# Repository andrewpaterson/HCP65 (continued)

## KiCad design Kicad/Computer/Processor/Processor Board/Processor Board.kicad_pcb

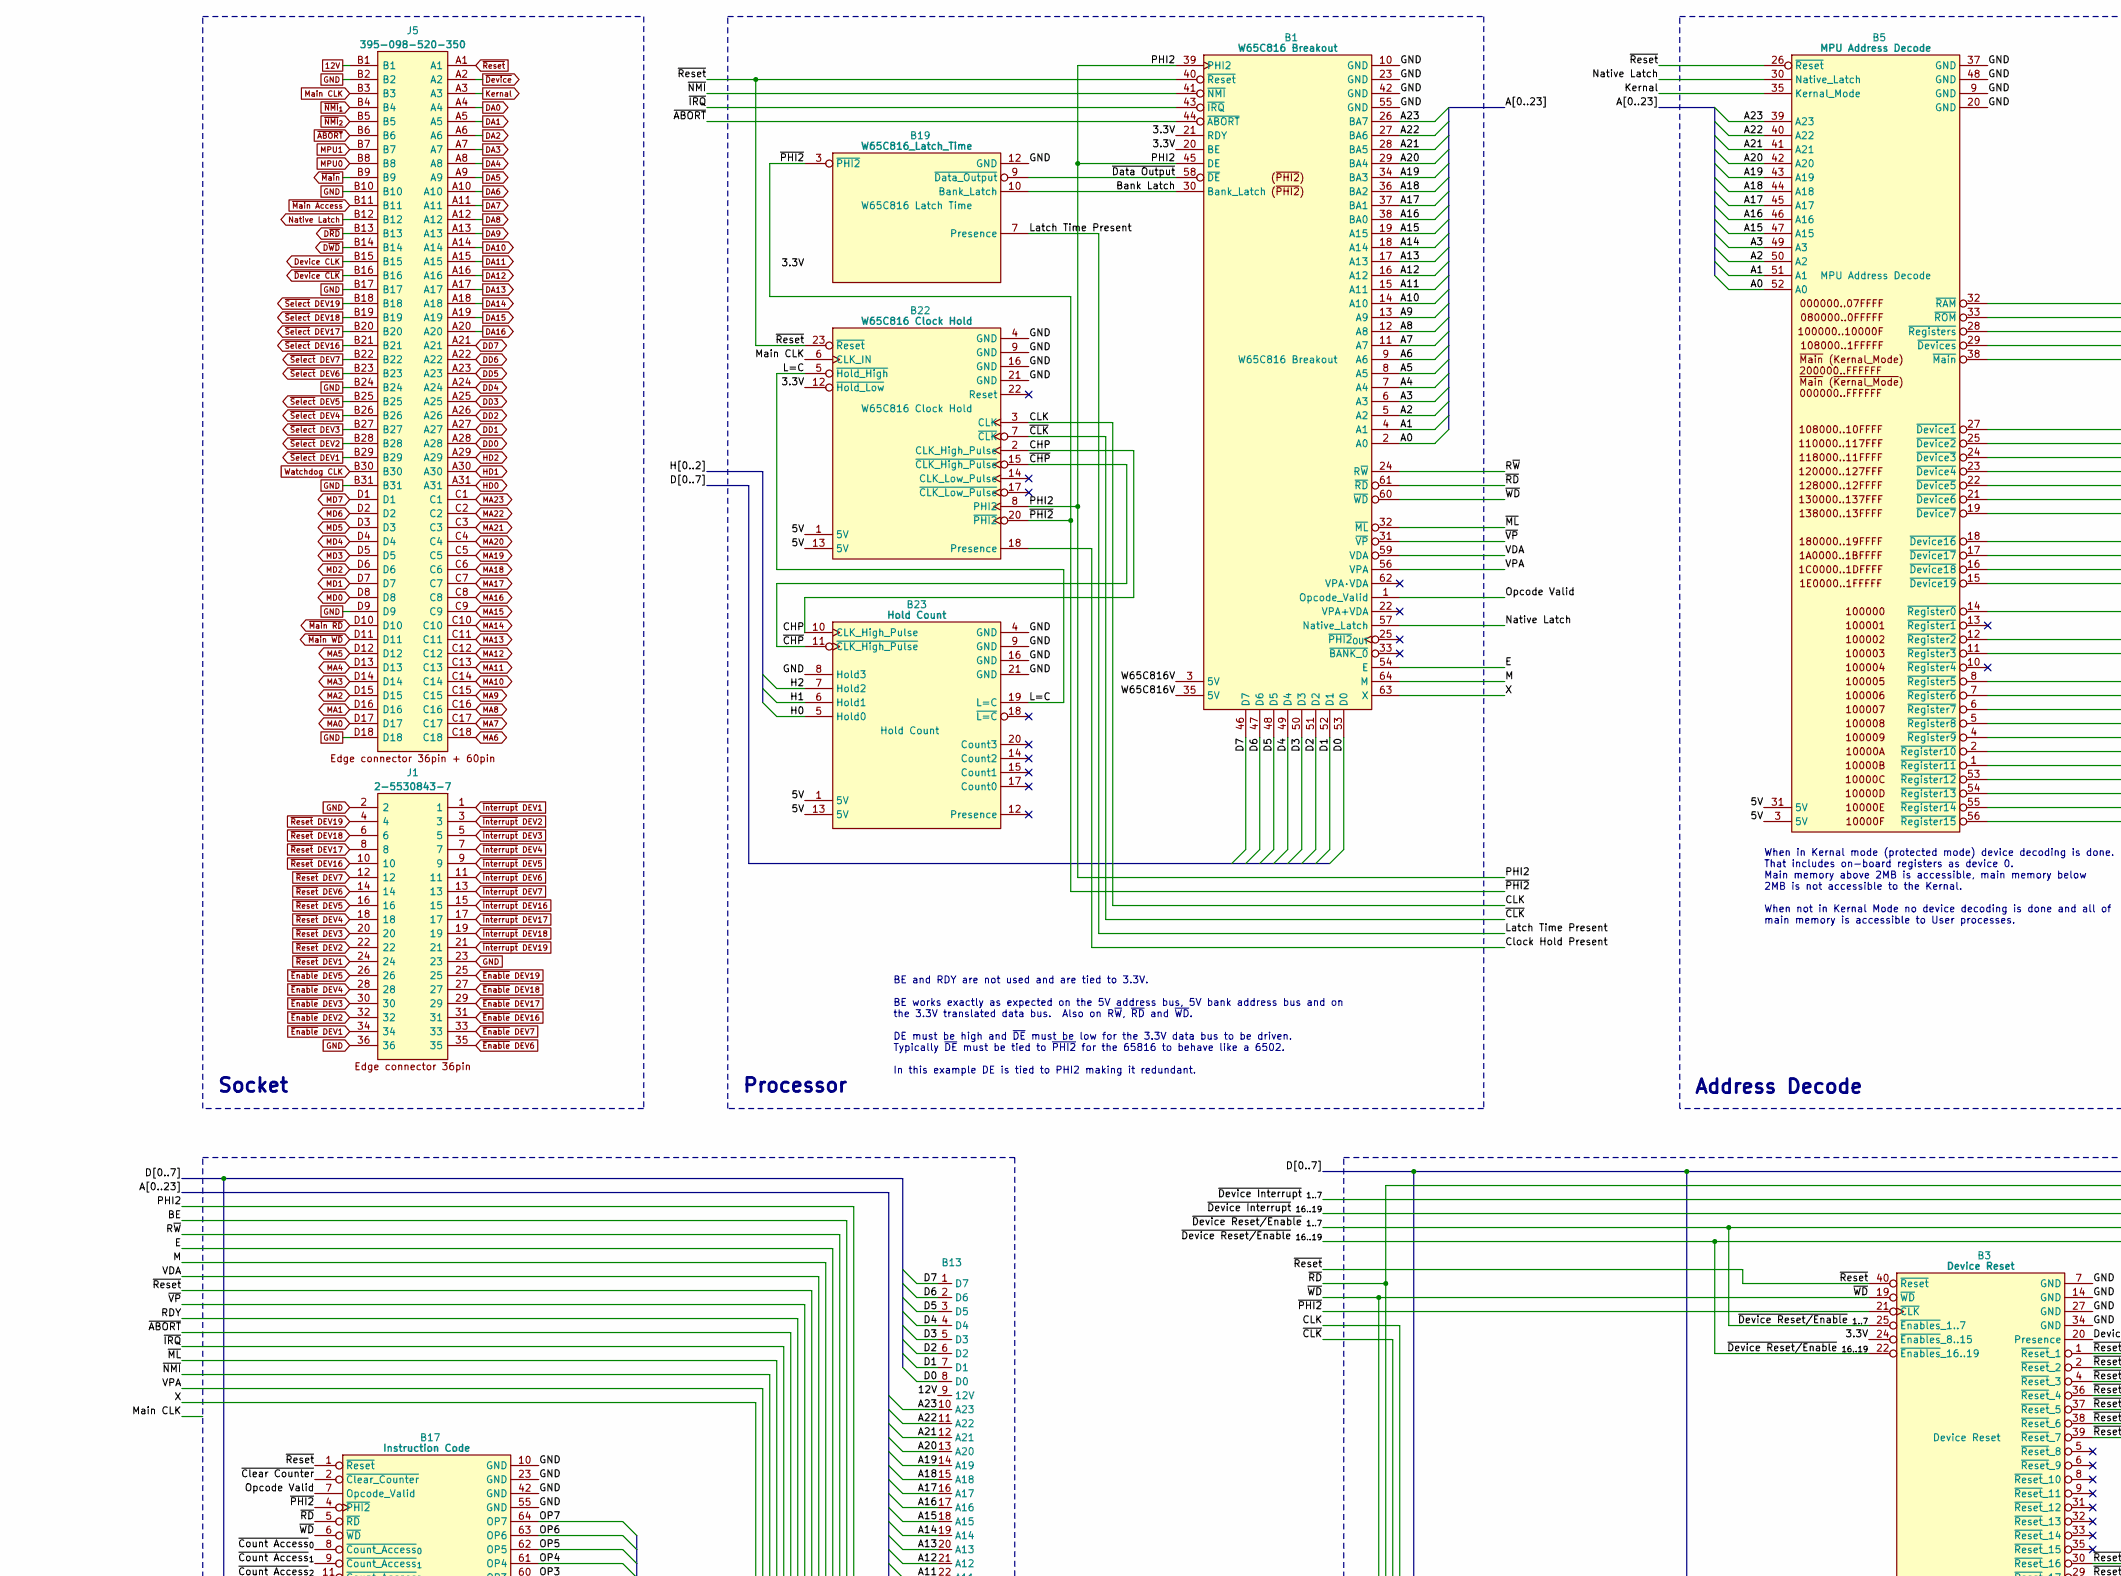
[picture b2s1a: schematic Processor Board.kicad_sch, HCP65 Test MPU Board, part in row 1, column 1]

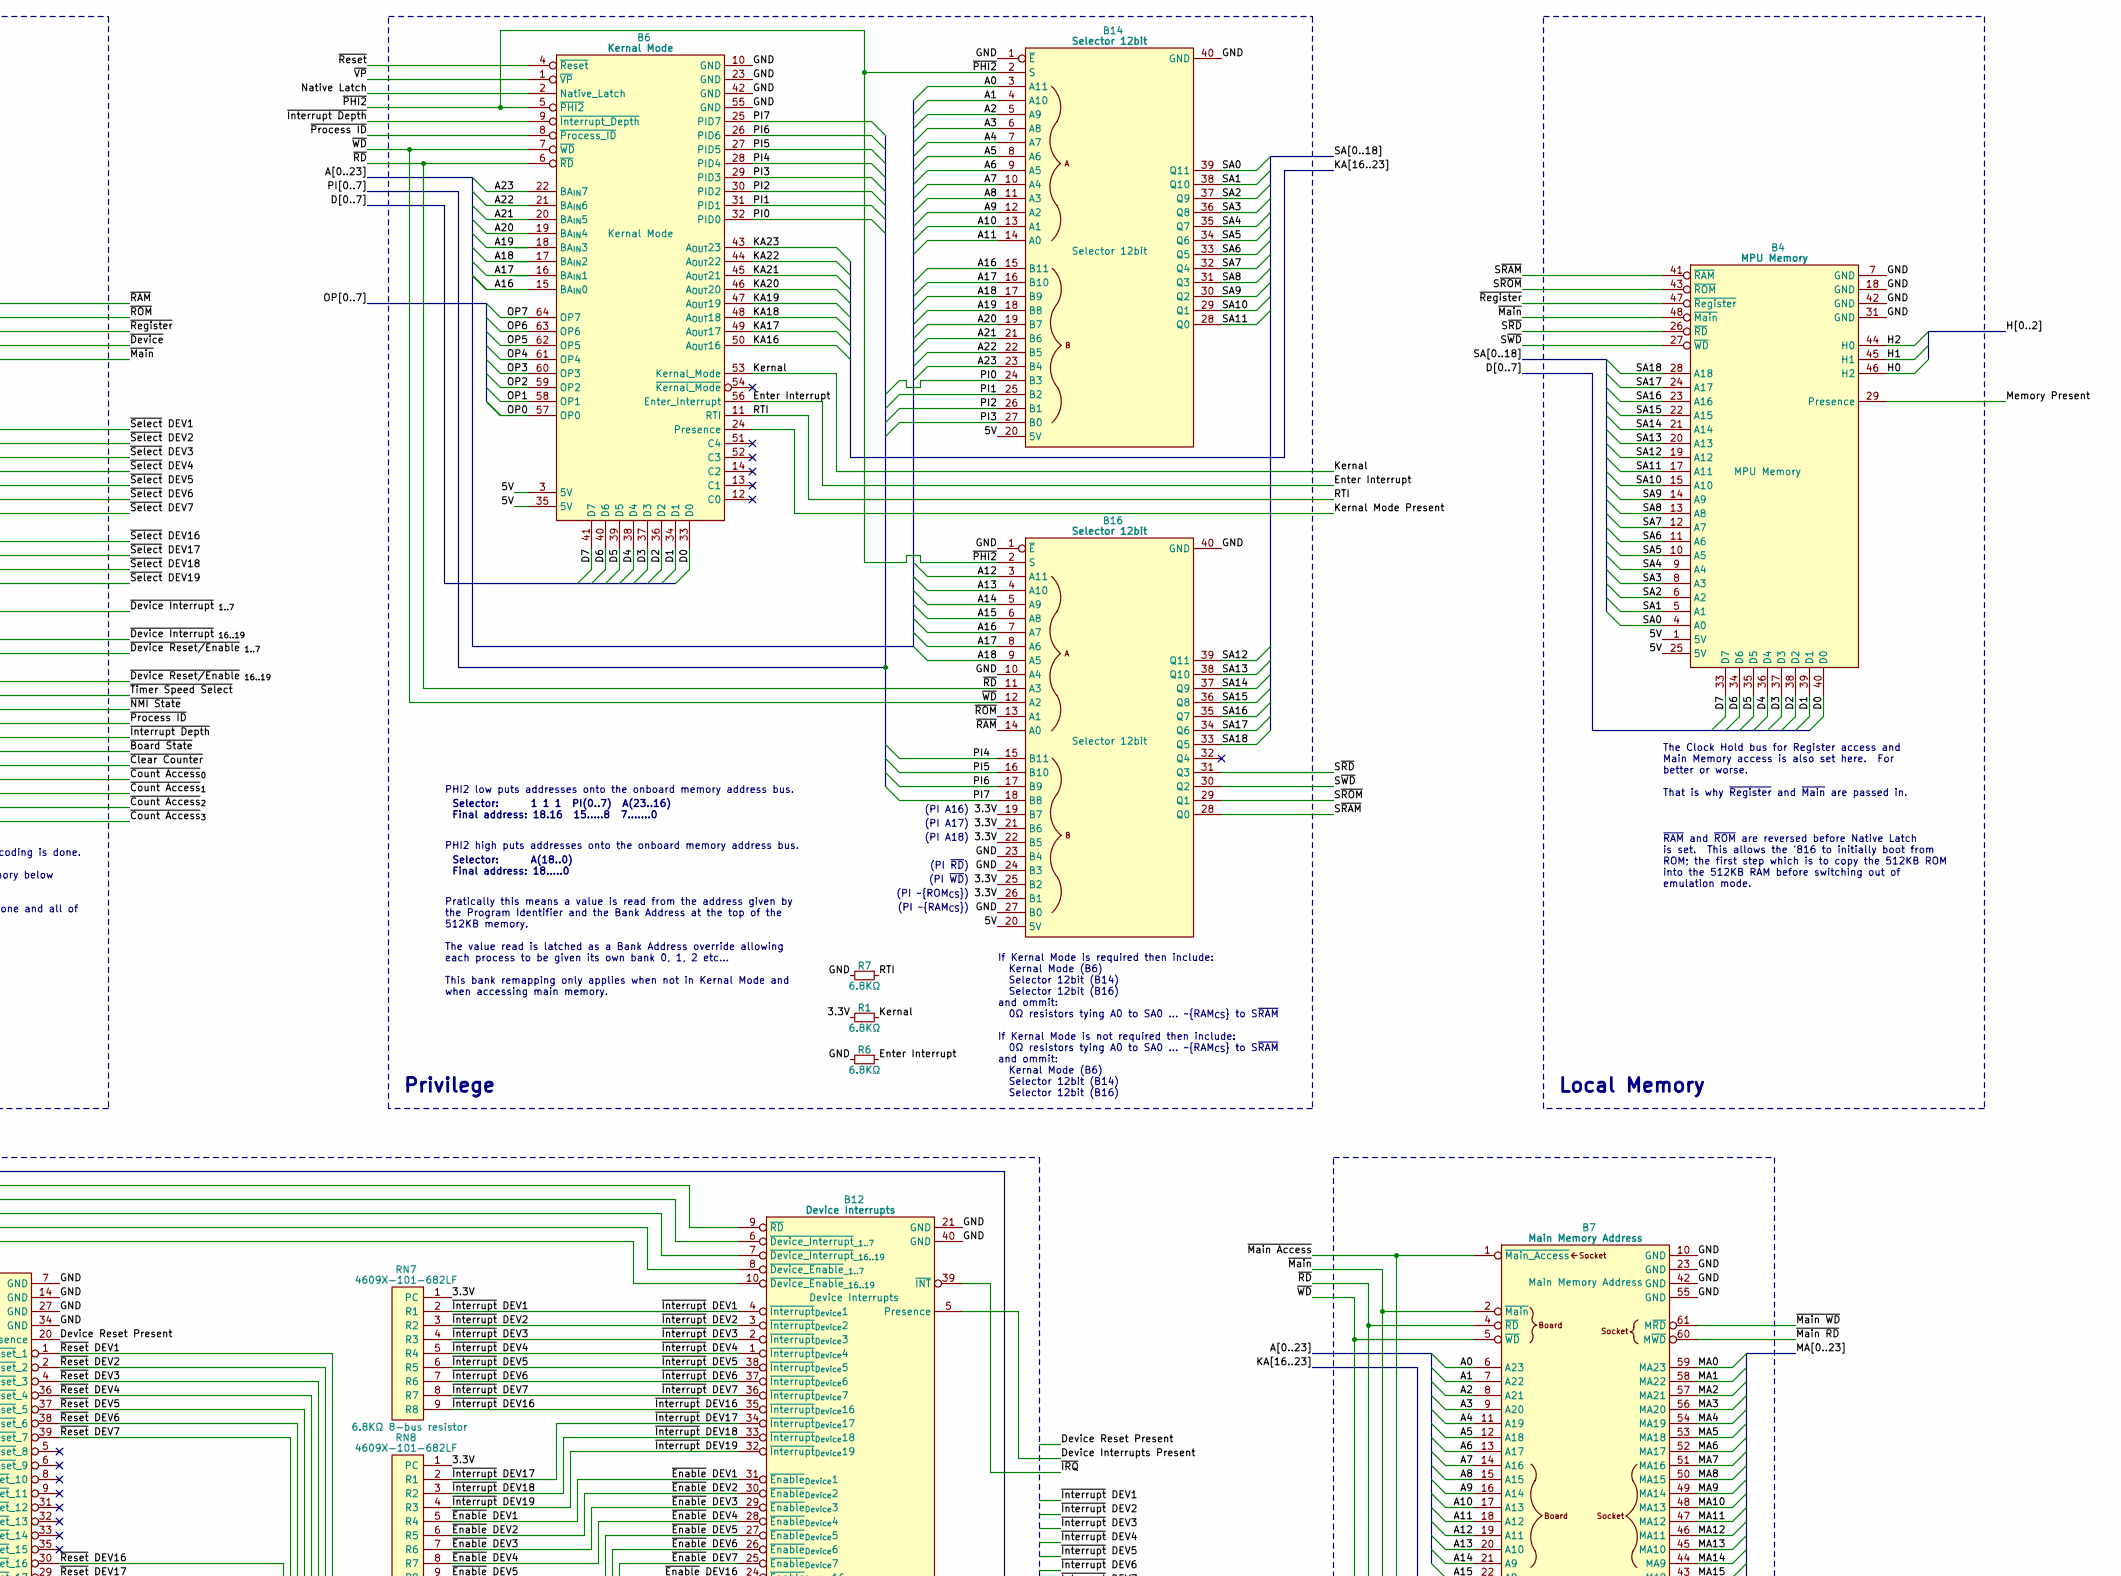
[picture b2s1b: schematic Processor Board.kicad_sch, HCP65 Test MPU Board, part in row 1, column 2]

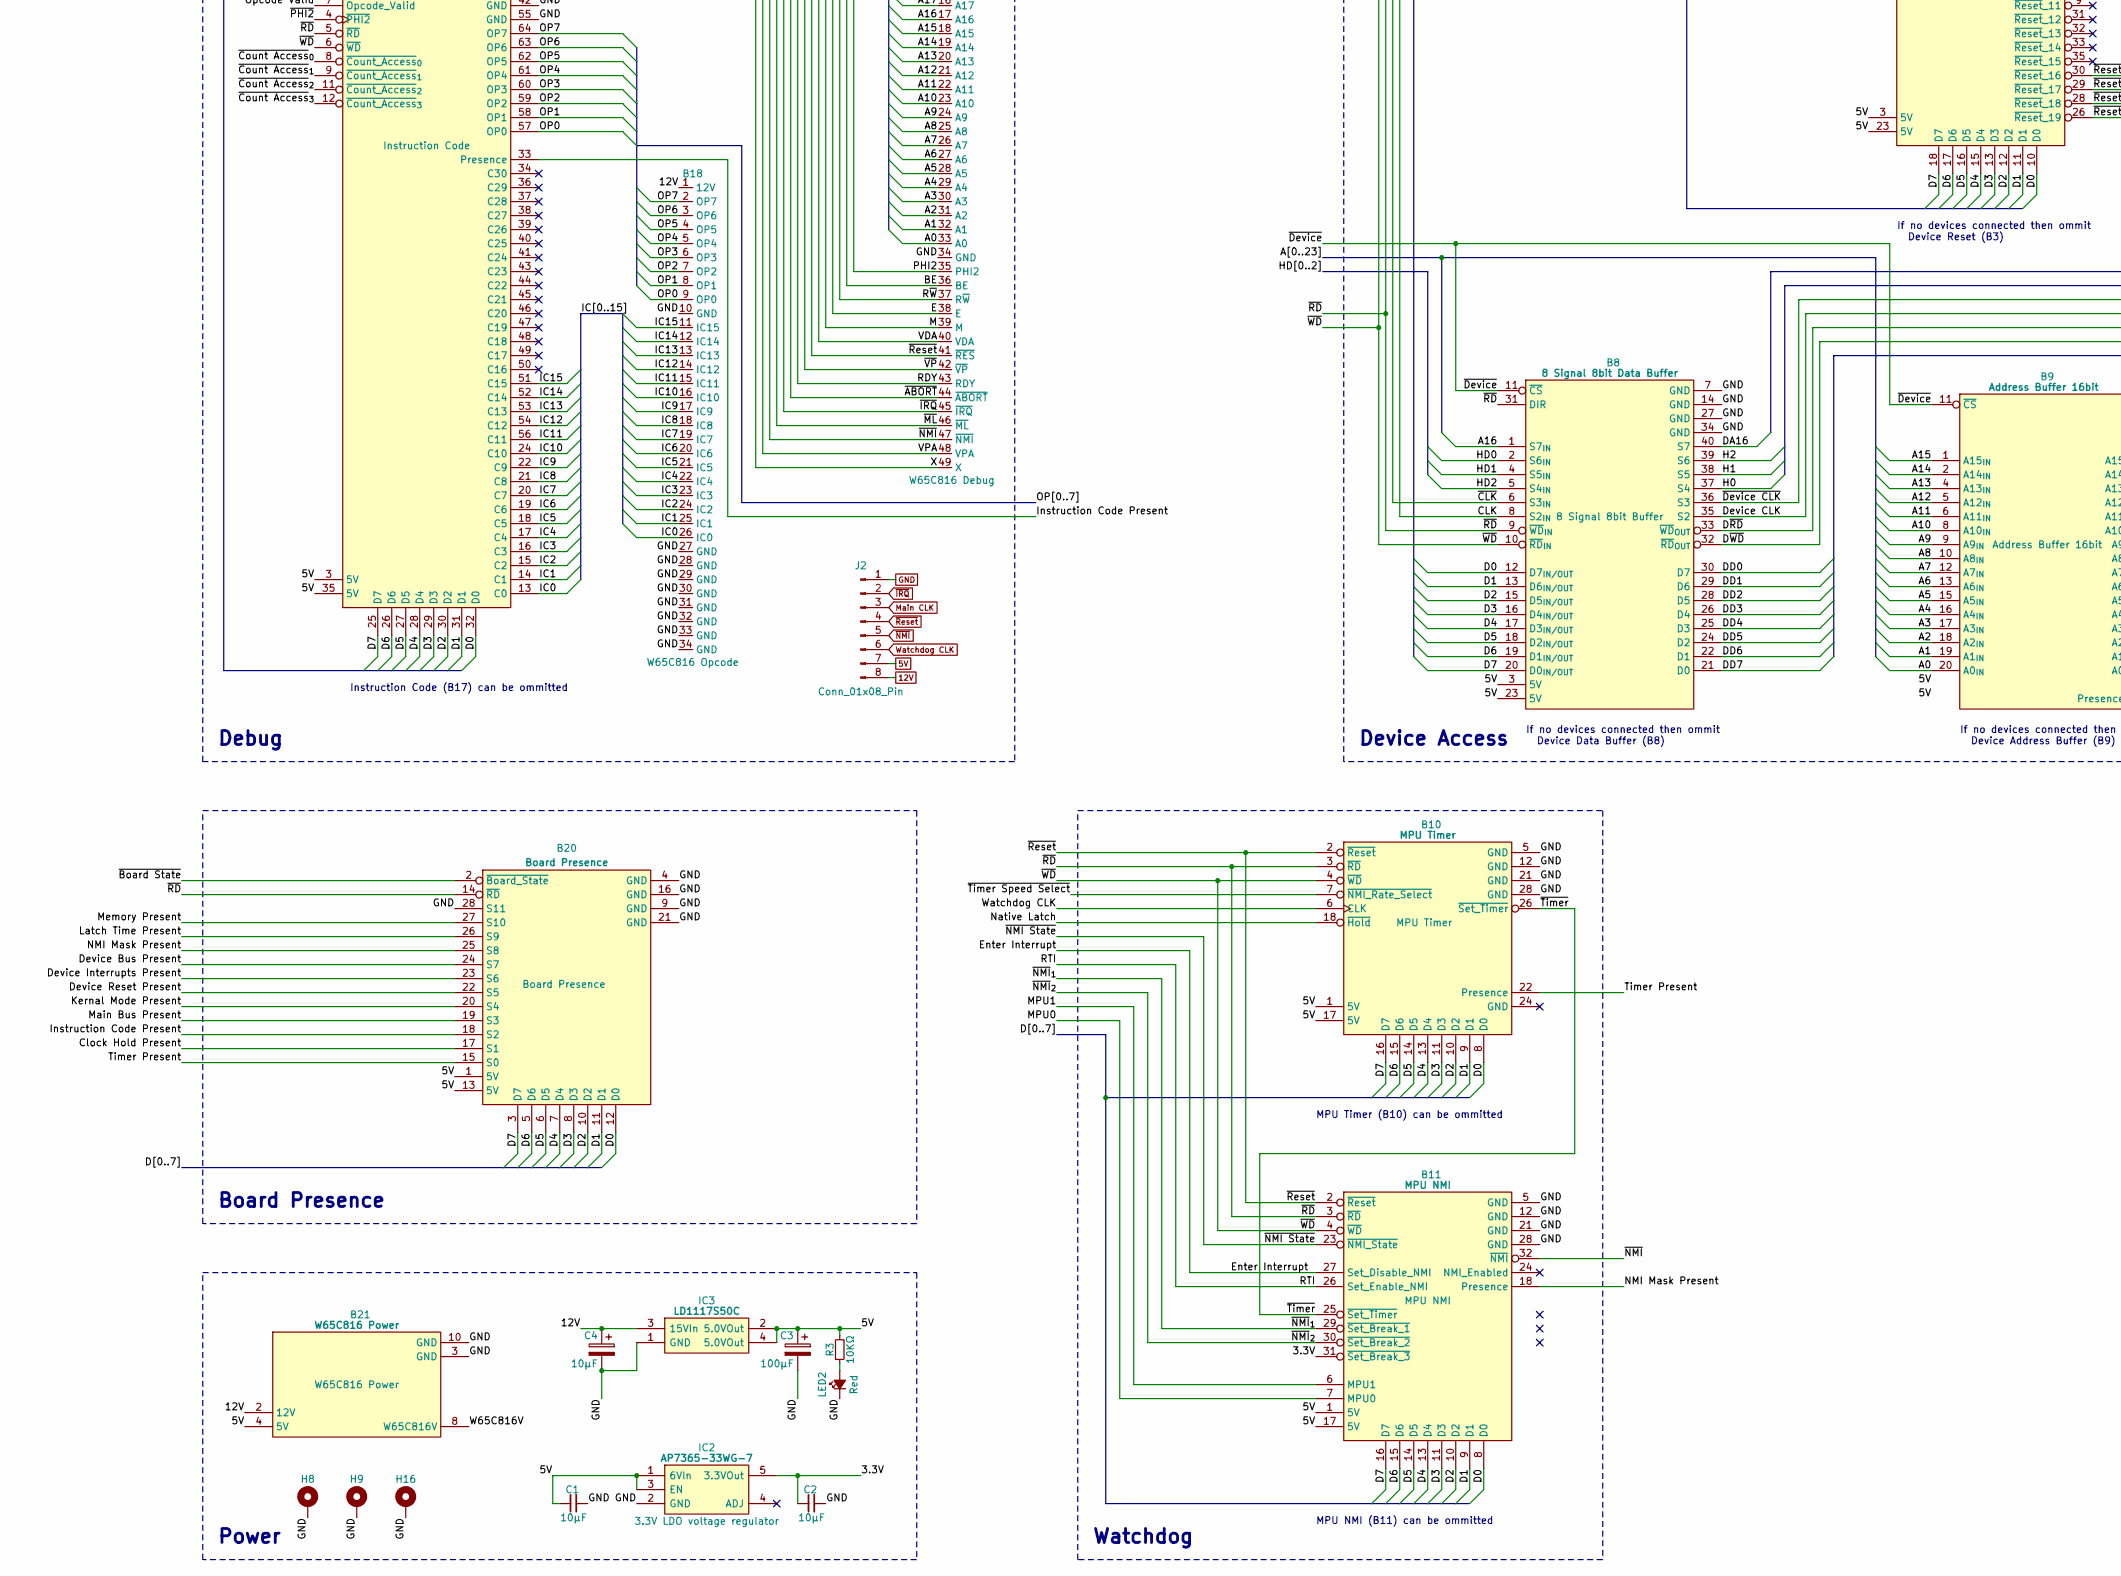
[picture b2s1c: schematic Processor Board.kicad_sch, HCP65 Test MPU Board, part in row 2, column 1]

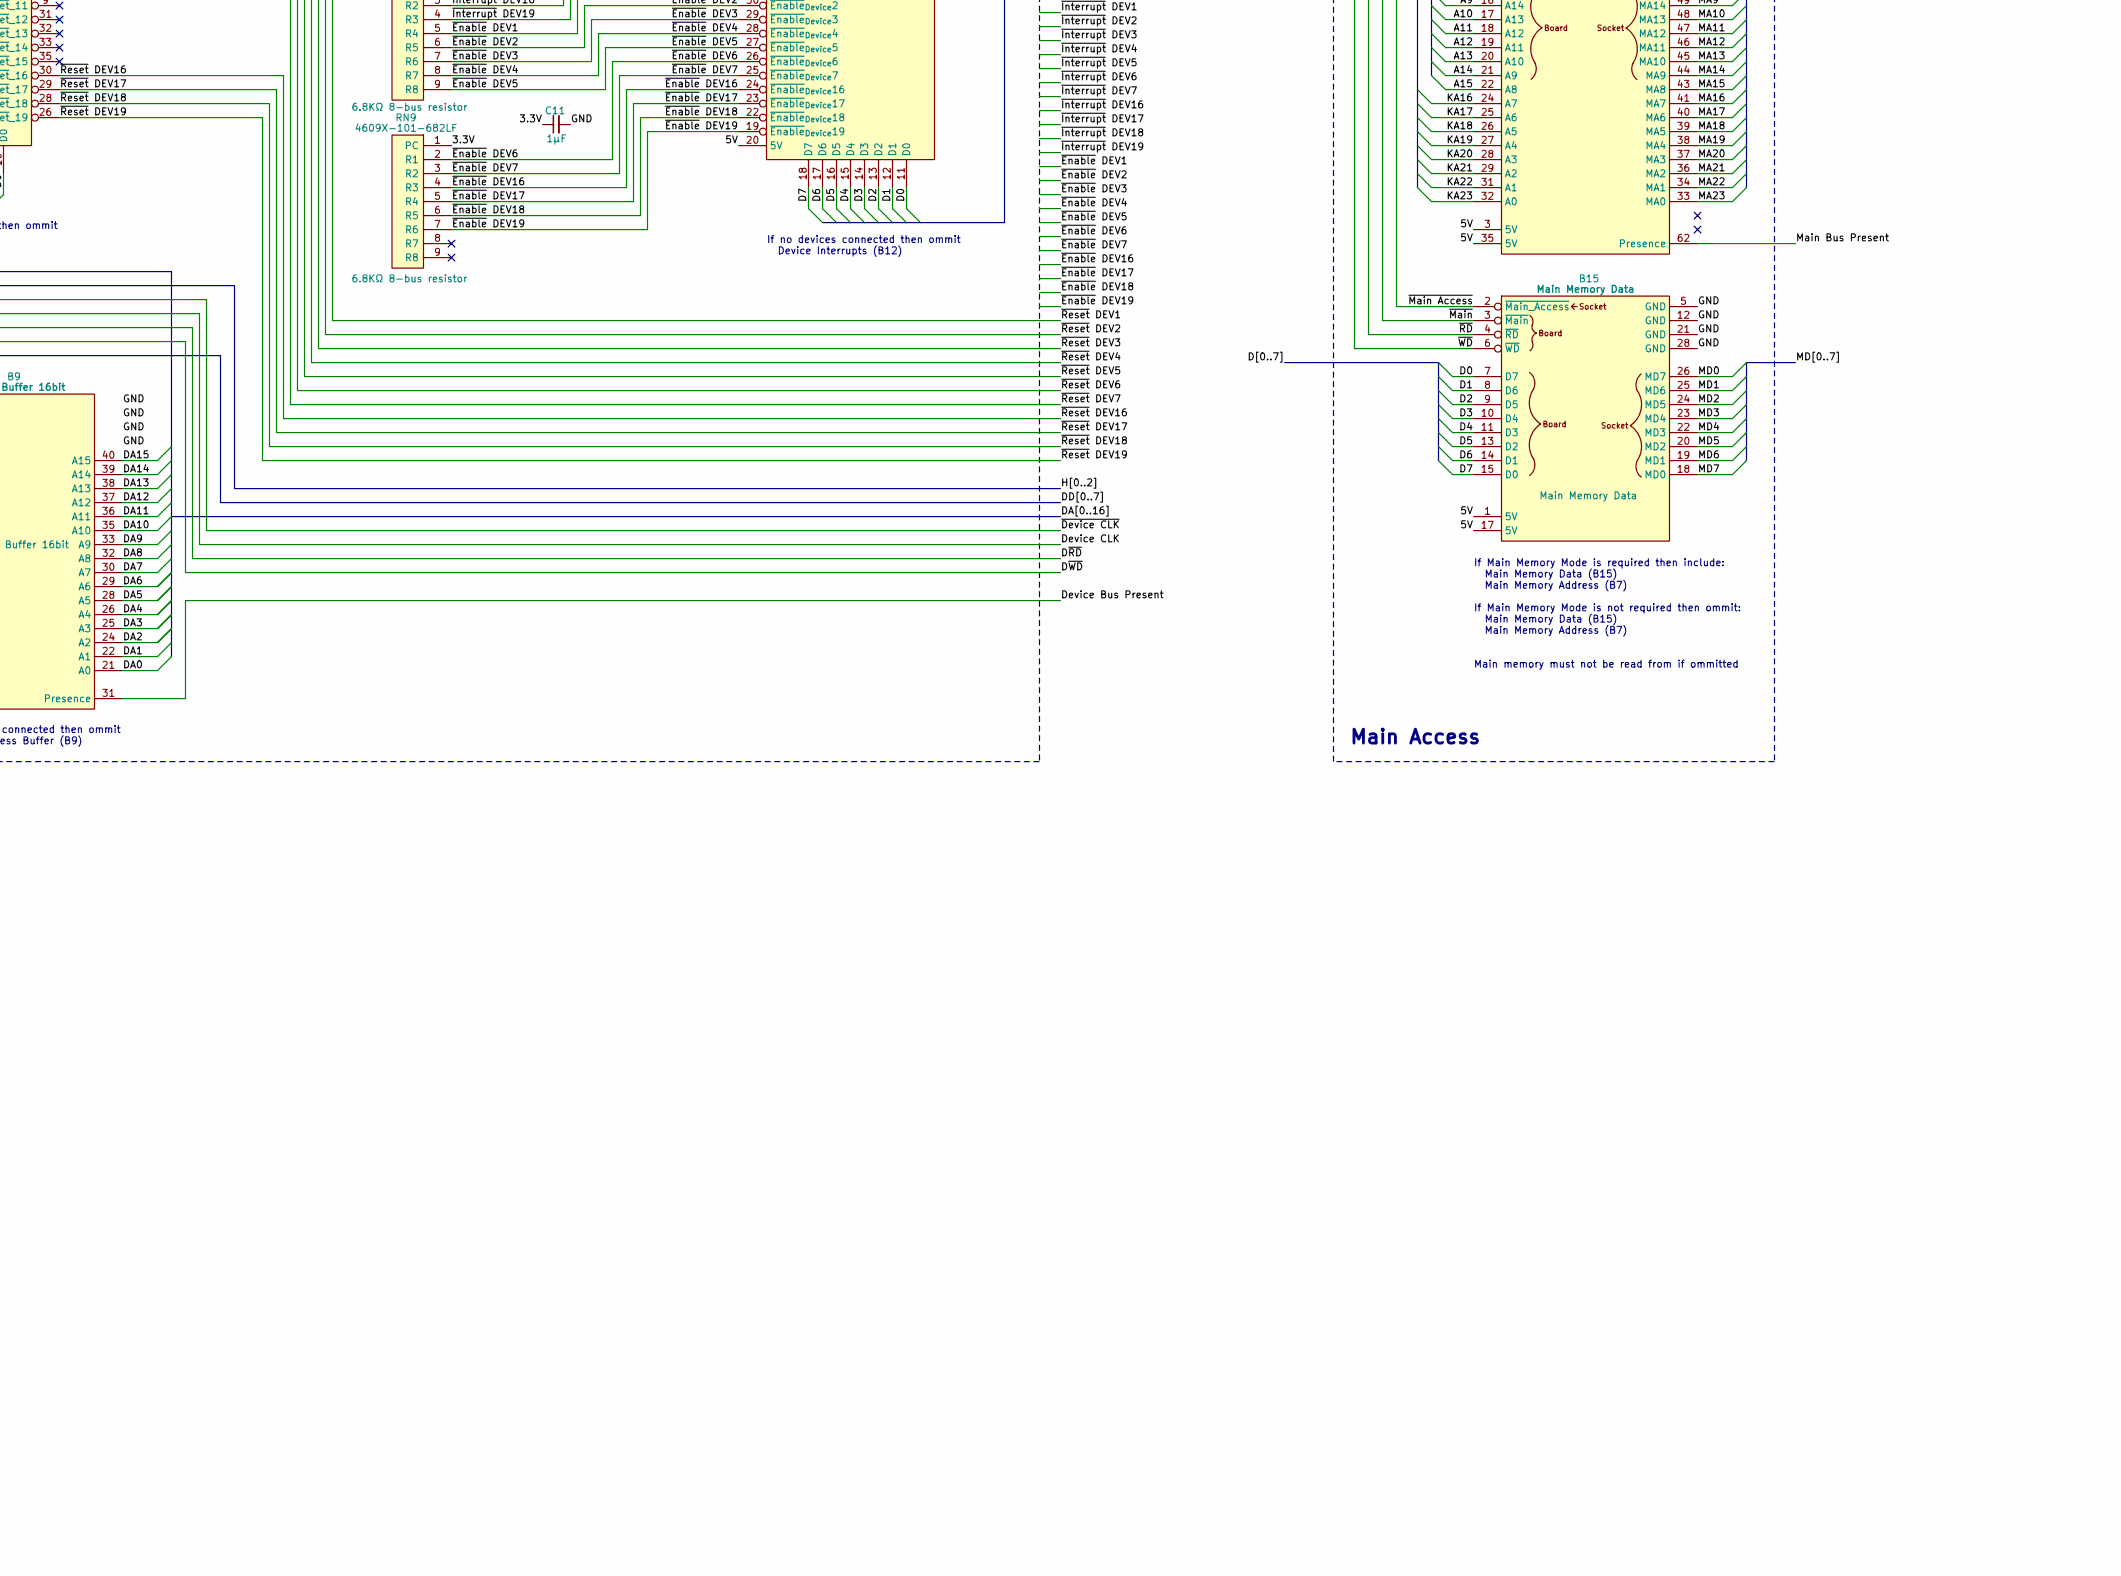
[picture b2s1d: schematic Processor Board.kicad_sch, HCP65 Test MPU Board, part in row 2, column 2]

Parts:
B1: W65C816 Breakout; HCP65_W65C816_Breakout
B3: Device Reset; HCP65_Device_Reset
B4: MPU Memory; HCP65_MPU_Memory
B5: MPU Address Decode; HCP65_MPU_Address_Decode
B6: Kernal Mode; HCP65_Kernal_Mode
B7: Main Memory Address; HCP65_Main_Memory_Address
B8: 8 Signal 8bit Data Buffer; HCP65_Data_and_Signal_Buffer
B9: Address Buffer 16bit; HCP65_Address_Buffer_16bit
B10: MPU Timer; HCP65_MPU_Timer
B11: MPU NMI; HCP65_MPU_NMI
B12: Device Interrupts; HCP65_Device_Interrupts
B13: W65C816 Debug; HCP65_W65C816_Debug_Display
B14, B16: Selector 12bit; HCP65_Selector_12bit
B15: Main Memory Data; HCP65_Main_Memory_Data
B17: Instruction Code; HCP65_Instruction_Code
B18: W65C816 Opcode; HCP65_W65C816_Debug_Instruction
B19: W65C816_Latch_Time; HCP65_W65C816_Latch_Time
B20: Board Presence; HCP65_Board_Presence
B21: W65C816 Power; HCP65_W65C816_Power
B22: W65C816 Clock Hold; HCP65_W65C816_Clock_Hold
B23: Hold Count; HCP65_Hold_Count
C1, C2: 10µF; C_0805
C3: 100μF; CP_Radial_D4.0mm_P2.00mm
C4: 10μF; CP_Radial_D4.0mm_P2.00mm
C11: 1μF; C_0805
H8, H9, H16: MountingHole_Pad; HCP65_MountingHole_M3_
IC2: AP7365-33WG-7; SOT95P285X130-5N; Manufacturer_Part_Number AP7365-33WG-7; Mouser Part Number 621-AP7365-33WG-7
IC3: LD1117S50C; LD1117S33C; Manufacturer_Part_Number LD1117S50C
J1: 2-5530843-7; 36pin Edge Connector; Manufacturer_Part_Number 2-5530843-7; Mouser Part Number 571-2-5530843-7
J2: Conn_01x08_Pin; PinHeader_1x08_P2.54mm_Vertical
J5: 395-098-520-350; 98pin Edge Connector; Manufacturer_Part_Number 395-098-520-350; Mouser Part Number 587-395-098-520-350
LED2: Red; LED_D5.0mm
R1, R6, R7: 6.8KΩ; R_0805
R3: 10KΩ; R_0805
RN7, RN8, RN9: 4609X-101-682LF; 4609X; Manufacturer_Part_Number 4609X-101-682LF; Mouser Part Number 652-4609X-1LF-6.8K

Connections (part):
5V: B3.3 (5V), B3.23 (5V), B4.1 (5V), B4.25 (5V), B5.3 (5V), B5.31 (5V), B6.3 (5V), B6.35 (5V), B7.3 (5V), B7.35 (5V), B8.3 (5V), B8.23 (5V), B9.3 (5V), B9.23 (5V), B10.1 (5V), B10.17 (5V), B11.1 (5V), B11.17 (5V), B12.20 (5V), B14.20 (5V), B15.1 (5V), B15.17 (5V), B16.20 (5V), B17.3 (5V), B17.35 (5V), B20.1 (5V), B20.13 (5V), B21.4 (5V), B22.1 (5V), B22.13 (5V), B23.1 (5V), B23.13 (5V), C1.1, C3.1, IC2.1 (6VIn), IC2.3 (EN), IC3.2 (5.0VOut), IC3.4 (5.0VOut), J2.7, R3.2
12V: B13.9 (12V), B18.1 (12V), B21.2 (12V), C4.1, IC3.3 (15VIn), J2.8, J5.B1
/3.3V: B1.20 (BE), B1.21 (RDY), B3.24 (~Enables_8..15), B11.31 (~Set_Break_3), B16.19 (B7), B16.21 (B6), B16.22 (B5), B16.25 (B2), B16.26 (B1), B19.6 (3.3V), B22.12 (~Hold_Low), C2.1, C11.1, IC2.5 (3.3VOut), R1.2, RN7.1 (PC), RN8.1 (PC), RN9.1 (PC)
/A0: B1.2 (A0), B5.52 (A0), B7.6 (A23), B9.20 (A0_{IN}), B13.33 (A0), B14.3 (A11)
/A1: B1.4 (A1), B5.51 (A1), B7.7 (A22), B9.19 (A1_{IN}), B13.32 (A1), B14.4 (A10)
/A2: B1.5 (A2), B5.50 (A2), B7.8 (A21), B9.18 (A2_{IN}), B13.31 (A2), B14.5 (A9)
/A3: B1.6 (A3), B5.49 (A3), B7.9 (A20), B9.17 (A3_{IN}), B13.30 (A3), B14.6 (A8)
/A4: B1.7 (A4), B7.11 (A19), B9.16 (A4_{IN}), B13.29 (A4), B14.7 (A7)
/A5: B1.8 (A5), B7.12 (A18), B9.15 (A5_{IN}), B13.28 (A5), B14.8 (A6)
/A6: B1.9 (A6), B7.13 (A17), B9.13 (A6_{IN}), B13.27 (A6), B14.9 (A5)
/A7: B1.11 (A7), B7.14 (A16), B9.12 (A7_{IN}), B13.26 (A7), B14.10 (A4)
/A8: B1.12 (A8), B7.15 (A15), B9.10 (A8_{IN}), B13.25 (A8), B14.11 (A3)
/A9: B1.13 (A9), B7.16 (A14), B9.9 (A9_{IN}), B13.24 (A9), B14.12 (A2)
/A10: B1.14 (A10), B7.17 (A13), B9.8 (A10_{IN}), B13.23 (A10), B14.13 (A1)
/A11: B1.15 (A11), B7.18 (A12), B9.6 (A11_{IN}), B13.22 (A11), B14.14 (A0)
/A12: B1.16 (A12), B7.19 (A11), B9.5 (A12_{IN}), B13.21 (A12), B16.3 (A11)
/A13: B1.17 (A13), B7.20 (A10), B9.4 (A13_{IN}), B13.20 (A13), B16.4 (A10)
/A14: B1.18 (A14), B7.21 (A9), B9.2 (A14_{IN}), B13.19 (A14), B16.5 (A9)
/A15: B1.19 (A15), B5.47 (A15), B7.22 (A8), B9.1 (A15_{IN}), B13.18 (A15), B16.6 (A8)
/A16: B1.38 (BA0), B5.46 (A16), B6.15 (BA_{IN}0), B8.1 (S7_{IN}), B13.17 (A16), B14.15 (B11), B16.7 (A7)
/A17: B1.37 (BA1), B5.45 (A17), B6.16 (BA_{IN}1), B13.16 (A17), B14.16 (B10), B16.8 (A6)
/A18: B1.36 (BA2), B5.44 (A18), B6.17 (BA_{IN}2), B13.15 (A18), B14.17 (B9), B16.9 (A5)
/A19: B1.34 (BA3), B5.43 (A19), B6.18 (BA_{IN}3), B13.14 (A19), B14.18 (B8)
/A20: B1.29 (BA4), B5.42 (A20), B6.19 (BA_{IN}4), B13.13 (A20), B14.19 (B7)
/A21: B1.28 (BA5), B5.41 (A21), B6.20 (BA_{IN}5), B13.12 (A21), B14.21 (B6)
/A22: B1.27 (BA6), B5.40 (A22), B6.21 (BA_{IN}6), B13.11 (A22), B14.22 (B5)
/A23: B1.26 (BA7), B5.39 (A23), B6.22 (BA_{IN}7), B13.10 (A23), B14.23 (B4)
/BE: B13.36 (BE)
/Bank Latch: B1.30 (Bank_Latch), B19.10 (Bank_Latch)
/CHP: B22.2 (CLK_High_Pulse), B23.10 (CLK_High_Pulse)
/CLK: B8.8 (S2_{IN}), B22.3 (CLK)
/Clock Hold Present: B20.17 (S1), B22.18 (Presence)
/D0: B1.53 (D0), B3.10 (D0), B4.40 (D0), B6.33 (D0), B8.12 (D7_{IN/OUT}), B10.8 (D0), B11.8 (D0), B12.11 (D0), B13.8 (D0), B15.7 (D7), B17.32 (D0), B20.12 (D0)
/D1: B1.52 (D1), B3.11 (D1), B4.39 (D1), B6.34 (D1), B8.13 (D6_{IN/OUT}), B10.9 (D1), B11.9 (D1), B12.12 (D1), B13.7 (D1), B15.8 (D6), B17.31 (D1), B20.11 (D1)
/D2: B1.51 (D2), B3.12 (D2), B4.38 (D2), B6.36 (D2), B8.15 (D5_{IN/OUT}), B10.10 (D2), B11.10 (D2), B12.13 (D2), B13.6 (D2), B15.9 (D5), B17.30 (D2), B20.10 (D2)
/D3: B1.50 (D3), B3.13 (D3), B4.37 (D3), B6.37 (D3), B8.16 (D4_{IN/OUT}), B10.11 (D3), B11.11 (D3), B12.14 (D3), B13.5 (D3), B15.10 (D4), B17.29 (D3), B20.8 (D3)
/D4: B1.49 (D4), B3.15 (D4), B4.36 (D4), B6.38 (D4), B8.17 (D3_{IN/OUT}), B10.13 (D4), B11.13 (D4), B12.15 (D4), B13.4 (D4), B15.11 (D3), B17.28 (D4), B20.7 (D4)
/D5: B1.48 (D5), B3.16 (D5), B4.35 (D5), B6.39 (D5), B8.18 (D2_{IN/OUT}), B10.14 (D5), B11.14 (D5), B12.16 (D5), B13.3 (D5), B15.13 (D2), B17.27 (D5), B20.6 (D5)
/D6: B1.47 (D6), B3.17 (D6), B4.34 (D6), B6.40 (D6), B8.19 (D1_{IN/OUT}), B10.15 (D6), B11.15 (D6), B12.17 (D6), B13.2 (D6), B15.14 (D1), B17.26 (D6), B20.5 (D6)
/D7: B1.46 (D7), B3.18 (D7), B4.33 (D7), B6.41 (D7), B8.20 (D0_{IN/OUT}), B10.16 (D7), B11.16 (D7), B12.18 (D7), B13.1 (D7), B15.15 (D0), B17.25 (D7), B20.3 (D7)
/Device Bus Present: B9.31 (Presence), B20.24 (S7)
/Device Interrupts Present: B12.5 (Presence), B20.23 (S6)
/Device Reset Present: B3.20 (Presence), B20.22 (S5)
/E: B1.54 (E), B13.38 (E)
/Enter Interrupt: B6.56 (Enter_Interrupt), B11.27 (Set_Disable_NMI), R6.1
/H0: B4.46 (H2), B8.37 (S4), B23.5 (Hold0)
/H1: B4.45 (H1), B8.38 (S5), B23.6 (Hold1)
/H2: B4.44 (H0), B8.39 (S6), B23.7 (Hold2)
/IC0: B17.13 (C0), B18.26 (IC0)
/IC1: B17.14 (C1), B18.25 (IC1)
/IC2: B17.15 (C2), B18.24 (IC2)
/IC3: B17.16 (C3), B18.23 (IC3)
/IC4: B17.17 (C4), B18.22 (IC4)
/IC5: B17.18 (C5), B18.21 (IC5)
/IC6: B17.19 (C6), B18.20 (IC6)
/IC7: B17.20 (C7), B18.19 (IC7)
/IC8: B17.21 (C8), B18.18 (IC8)
/IC9: B17.22 (C9), B18.17 (IC9)
/IC10: B17.24 (C10), B18.16 (IC10)
/IC11: B17.56 (C11), B18.15 (IC11)
/IC12: B17.54 (C12), B18.14 (IC12)
/IC13: B17.53 (C13), B18.13 (IC13)
/IC14: B17.52 (C14), B18.12 (IC14)
/IC15: B17.51 (C15), B18.11 (IC15)
/Instruction Code Present: B17.33 (Presence), B20.18 (S2)
/KA16: B6.50 (A_{OUT}16), B7.24 (A7)
/KA17: B6.49 (A_{OUT}17), B7.25 (A6)
/KA18: B6.48 (A_{OUT}18), B7.26 (A5)
/KA19: B6.47 (A_{OUT}19), B7.27 (A4)
/KA20: B6.46 (A_{OUT}20), B7.28 (A3)
/KA21: B6.45 (A_{OUT}21), B7.29 (A2)
/KA22: B6.44 (A_{OUT}22), B7.31 (A1)
/KA23: B6.43 (A_{OUT}23), B7.32 (A0)
/Kernal Mode Present: B6.24 (Presence), B20.20 (S4)
/L=C: B22.5 (~Hold_High), B23.19 (L=C)
/Latch Time Present: B19.7 (Presence), B20.26 (S9)
/M: B1.64 (M), B13.39 (M)
/Main Bus Present: B7.62 (Presence), B20.19 (S3)
/Memory Present: B4.29 (Presence), B20.27 (S10)
/NMI Mask Present: B11.18 (Presence), B20.25 (S8)
/OP0: B6.57 (OP0), B17.57 (OP0), B18.9 (OP0)
/OP1: B6.58 (OP1), B17.58 (OP1), B18.8 (OP1)
/OP2: B6.59 (OP2), B17.59 (OP2), B18.7 (OP2)
/OP3: B6.60 (OP3), B17.60 (OP3), B18.6 (OP3)
/OP4: B6.61 (OP4), B17.61 (OP4), B18.5 (OP4)
/OP5: B6.62 (OP5), B17.62 (OP5), B18.4 (OP5)
/OP6: B6.63 (OP6), B17.63 (OP6), B18.3 (OP6)
/OP7: B6.64 (OP7), B17.64 (OP7), B18.2 (OP7)
/Opcode Valid: B1.1 (Opcode_Valid), B17.7 (Opcode_Valid)
/PHI2: B1.39 (PHI2), B1.45 (DE), B13.35 (PHI2), B22.8 (PHI2)
/PI0: B6.32 (PID0), B14.24 (B3)
/PI1: B6.31 (PID1), B14.25 (B2)
/PI2: B6.30 (PID2), B14.26 (B1)
/PI3: B6.29 (PID3), B14.27 (B0)
/PI4: B6.28 (PID4), B16.15 (B11)
/PI5: B6.27 (PID5), B16.16 (B10)
/PI6: B6.26 (PID6), B16.17 (B9)
/PI7: B6.25 (PID7), B16.18 (B8)
/RDY: B13.43 (RDY)
/RTI: B6.11 (RTI), B11.26 (Set_Enable_NMI), R7.1
/R~W: B1.24 (R~W), B13.37 (R~W)
/SA0: B4.4 (A0), B14.39 (Q11)
/SA1: B4.5 (A1), B14.38 (Q10)
/SA2: B4.6 (A2), B14.37 (Q9)
/SA3: B4.8 (A3), B14.36 (Q8)
/SA4: B4.9 (A4), B14.35 (Q7)
/SA5: B4.10 (A5), B14.34 (Q6)
/SA6: B4.11 (A6), B14.33 (Q5)
/SA7: B4.12 (A7), B14.32 (Q4)
/SA8: B4.13 (A8), B14.31 (Q3)
/SA9: B4.14 (A9), B14.30 (Q2)
/SA10: B4.15 (A10), B14.29 (Q1)
/SA11: B4.17 (A11), B14.28 (Q0)
/SA12: B4.19 (A12), B16.39 (Q11)
/SA13: B4.20 (A13), B16.38 (Q10)
/SA14: B4.21 (A14), B16.37 (Q9)
/SA15: B4.22 (A15), B16.36 (Q8)
/SA16: B4.23 (A16), B16.35 (Q7)
/SA17: B4.24 (A17), B16.34 (Q6)
/SA18: B4.28 (A18), B16.33 (Q5)
/S~RAM: B4.41 (~RAM), B16.28 (Q0)
/S~RD: B4.26 (~RD), B16.31 (Q3)
/S~ROM: B4.43 (~ROM), B16.29 (Q1)
/S~WD: B4.27 (~WD), B16.30 (Q2)
/Timer Present: B10.22 (Presence), B20.15 (S0)
/VDA: B1.59 (VDA), B13.40 (VDA)
/VPA: B1.56 (VPA), B13.48 (VPA)
/W65C816V: B1.3 (5V), B1.35 (5V), B21.8 (W65C816V)
/X: B1.63 (X), B13.49 (X)
/~Board State: B5.2 (~Register10), B20.2 (~Board_State)
/~CHP: B22.15 (~CLK_High_Pulse), B23.11 (~CLK_High_Pulse)
/~CLK: B8.6 (S3_{IN}), B22.7 (~CLK)
/~Clear Counter: B5.1 (~Register11), B17.2 (~Clear_Counter)
/~Count Access_{0}: B5.53 (~Register12), B17.8 (~Count_Access_{0})
/~Count Access_{1}: B5.54 (~Register13), B17.9 (~Count_Access_{1})
/~Count Access_{2}: B5.55 (~Register14), B17.11 (~Count_Access_{2})
/~Count Access_{3}: B5.56 (~Register15), B17.12 (~Count_Access_{3})
/~Data Output: B1.58 (~DE), B19.9 (~Data_Output)
/~Device Interrupt_{ 1..7}: B5.14 (~Register0), B12.6 (~Device_Interrupt_{_1..7})
/~Device Interrupt_{ 16..19}: B5.12 (~Register2), B12.7 (~Device_Interrupt_{_16..19})
/~Device Reset/Enable_{ 1..7}: B3.25 (~Enables_1..7), B5.11 (~Register3), B12.8 (~Device_Enable_{_1..7})
/~Device Reset/Enable_{ 16..19}: B3.22 (~Enables_16..19), B5.8 (~Register5), B12.10 (~Device_Enable_{_16..19})
/~Interrupt Depth: B5.4 (~Register9), B6.9 (~Interrupt_Depth)
/~ML: B1.32 (~ML), B13.46 (~ML)
/~NMI State: B5.6 (~Register7), B11.23 (~NMI_State)
/~PHI2: B3.21 (~CLK), B6.5 (~PHI2), B14.2 (S), B16.2 (S), B17.4 (~PHI2), B19.3 (~PHI2), B22.20 (~PHI2)
/~Process ID: B5.5 (~Register8), B6.8 (~Process_ID)
/~RAM: B5.32 (~RAM), B16.14 (A0)
/~RD: B1.61 (~RD), B6.6 (~RD), B7.4 (~RD), B8.9 (~WD_{IN}), B8.31 (DIR), B10.3 (~RD), B11.3 (~RD), B12.9 (~RD), B15.4 (~RD), B16.11 (A3), B17.5 (~RD), B20.14 (~RD)
/~ROM: B5.33 (~ROM), B16.13 (A1)
/~Register: B4.47 (~Register), B5.28 (~Registers)
/~Timer Speed Select: B5.7 (~Register6), B10.7 (~NMI_Rate_Select)
/~Timer: B10.26 (~Set_Timer), B11.25 (~Set_Timer)
/~VP: B1.31 (~VP), B6.1 (~VP), B13.42 (~VP)
/~WD: B1.60 (~WD), B3.19 (~WD), B6.7 (~WD), B7.5 (~WD), B8.10 (~RD_{IN}), B10.4 (~WD), B11.4 (~WD), B15.6 (~WD), B16.12 (A2), B17.6 (~WD)
DA0: B9.21 (A0), J5.A4
DA1: B9.22 (A1), J5.A5
DA2: B9.24 (A2), J5.A6
DA3: B9.25 (A3), J5.A7
DA4: B9.26 (A4), J5.A8
DA5: B9.28 (A5), J5.A9
DA6: B9.29 (A6), J5.A10
DA7: B9.30 (A7), J5.A11
DA8: B9.32 (A8), J5.A12
DA9: B9.33 (A9), J5.A13
DA10: B9.35 (A10), J5.A14
DA11: B9.36 (A11), J5.A15
DA12: B9.37 (A12), J5.A16
DA13: B9.38 (A13), J5.A17
DA14: B9.39 (A14), J5.A18
DA15: B9.40 (A15), J5.A19
DA16: B8.40 (S7), J5.A20
DD0: B8.30 (D7), J5.A28
DD1: B8.29 (D6), J5.A27
DD2: B8.28 (D5), J5.A26
DD3: B8.26 (D4), J5.A25
DD4: B8.25 (D3), J5.A24
DD5: B8.24 (D2), J5.A23
DD6: B8.22 (D1), J5.A22
DD7: B8.21 (D0), J5.A21
Device CLK: B8.35 (S2), J5.B15
D~RD: B8.33 (~WD_{OUT}), J5.B13
D~WD: B8.32 (~RD_{OUT}), J5.B14
GND: B1.10 (GND), B1.23 (GND), B1.42 (GND), B1.55 (GND), B3.7 (GND), B3.14 (GND), B3.27 (GND), B3.34 (GND), B4.7 (GND), B4.18 (GND), B4.31 (GND), B4.42 (GND), B5.9 (GND), B5.20 (GND), B5.37 (GND), B5.48 (GND), B6.10 (GND), B6.23 (GND), B6.42 (GND), B6.55 (GND), B7.10 (GND), B7.23 (GND), B7.42 (GND), B7.55 (GND), B8.7 (GND), B8.14 (GND), B8.27 (GND), B8.34 (GND), B9.7 (GND), B9.14 (GND), B9.27 (GND), B9.34 (GND), B10.5 (GND), B10.12 (GND), B10.21 (GND), B10.28 (GND), B11.5 (GND), B11.12 (GND), B11.21 (GND), B11.28 (GND), B12.21 (GND), B12.40 (GND), B13.34 (GND), B14.1 (~E), B14.40 (GND), B15.5 (GND), B15.12 (GND), B15.21 (GND), B15.28 (GND), B16.1 (~E), B16.10 (A4), B16.23 (B4), B16.24 (B3), B16.27 (B0), B16.40 (GND), B17.10 (GND), B17.23 (GND), B17.42 (GND), B17.55 (GND), B18.10 (GND), B18.27 (GND), B18.28 (GND), B18.29 (GND), B18.30 (GND), B18.31 (GND), B18.32 (GND), B18.33 (GND), B18.34 (GND), B19.12 (GND), B20.4 (GND), B20.9 (GND), B20.16 (GND), B20.21 (GND), B20.28 (S11), B21.3 (GND), B21.10 (GND), B22.4 (GND), B22.9 (GND), B22.16 (GND), B22.21 (GND), B23.4 (GND)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
HD0: B8.2 (S6_{IN}), J5.A31
HD1: B8.4 (S5_{IN}), J5.A30
HD2: B8.5 (S4_{IN}), J5.A29
Kernal: B5.35 (Kernal_Mode), B6.53 (Kernal_Mode), J5.A3, R1.1
MA0: B7.59 (MA23), J5.D17
MA1: B7.58 (MA22), J5.D16
MA2: B7.57 (MA21), J5.D15
MA3: B7.56 (MA20), J5.D14
MA4: B7.54 (MA19), J5.D13
MA5: B7.53 (MA18), J5.D12
MA6: B7.52 (MA17), J5.C18
MA7: B7.51 (MA16), J5.C17
MA8: B7.50 (MA15), J5.C16
MA9: B7.49 (MA14), J5.C15
MA10: B7.48 (MA13), J5.C14
MA11: B7.47 (MA12), J5.C13
MA12: B7.46 (MA11), J5.C12
MA13: B7.45 (MA10), J5.C11
MA14: B7.44 (MA9), J5.C10
MA15: B7.43 (MA8), J5.C9
MA16: B7.41 (MA7), J5.C8
MA17: B7.40 (MA6), J5.C7
MA18: B7.39 (MA5), J5.C6
MA19: B7.38 (MA4), J5.C5
MA20: B7.37 (MA3), J5.C4
MA21: B7.36 (MA2), J5.C3
MA22: B7.34 (MA1), J5.C2
MA23: B7.33 (MA0), J5.C1
MD0: B15.26 (MD7), J5.D8
MD1: B15.25 (MD6), J5.D7
MD2: B15.24 (MD5), J5.D6
MD3: B15.23 (MD4), J5.D5
MD4: B15.22 (MD3), J5.D4
MD5: B15.20 (MD2), J5.D3
MD6: B15.19 (MD1), J5.D2
MD7: B15.18 (MD0), J5.D1
MPU0: B11.7 (MPU0), J5.B8
MPU1: B11.6 (MPU1), J5.B7
Main CLK: B22.6 (CLK_IN), J2.3, J5.B3
Native Latch: B1.57 (Native_Latch), B5.30 (Native_Latch), B6.2 (Native_Latch), B10.18 (~Hold), J5.B12
unnamed: LED2.2 (A), R3.1
Watchdog CLK: B10.6 (CLK), J2.6, J5.B30
~ABORT: B1.44 (~ABORT), B13.44 (~ABORT), J5.B6
~Device CLK: B8.36 (S3), J5.B16
~Device: B5.29 (~Devices), B8.11 (~CS), B9.11 (~CS), J5.A2
~Enable DEV1: B12.31 (~Enable_{Device}1), J1.34, RN8.5 (R4)
~Enable DEV2: B12.30 (~Enable_{Device}2), J1.32, RN8.6 (R5)
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
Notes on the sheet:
~{RAM} and ~{ROM} are reversed before Native Latch is set. This allows the '816 to initially boot from ROM; the first step which is to copy the 512KB ROM into the 512KB RAM before switching out of emulation mode.
The Clock Hold bus for Register access and Main Memory access is also set here. For better or worse. That is why ~{Register} and ~{Main} are passed in.
Selector: 1 1 1 PI(0..7) A(23..16) Final address: 18.16 15.....8 7.......0 Selector: A(18..0) Final address: 18.....0
Main Access
Board Presence
If Main Memory Mode is required then include: Main Memory Data (B15) Main Memory Address (B7) If Main Memory Mode is not required then ommit: Main Memory Data (B15) Main Memory Address (B7) Main memory must not be read from if ommitted
MPU Timer (B10) can be ommitted
Processor
(PI A18)
Privilege
Debug
MPU NMI (B11) can be ommitted
If no devices connected then ommit Device Reset (B3)
(PI ~{WD})
If no devices connected then ommit Device Address Buffer (B9)
BE and RDY are not used and are tied to 3.3V. BE works exactly as expected on the 5V address bus, 5V bank address bus and on the 3.3V translated data bus. Also on R~{W}, ~{RD} and ~{WD}. DE must be high and ~{DE} must be low for the 3.3V data bus to be driven. Typically ~{DE} must be tied to ~{PHI2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
Watchdog
Pratically this means a value is read from the address given by the Program Identifier and the Bank Address at the top of the 512KB memory. The value read is latched as a Bank Address override allowing each process to be given its own bank 0, 1, 2 etc... This bank remapping only applies when not in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
PHI2 low puts addresses onto the onboard memory address bus.
Socket
Local Memory
PHI2 high puts addresses onto the onboard memory address bus.
When in Kernal mode (protected mode) device decoding is done. That includes on-board registers as device 0. Main memory above 2MB is accessible, main memory below 2MB is not accessible to the Kernal. When not in Kernal Mode no device decoding is done and all of main memory is accessible to User pro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
If no devices connected then ommit Device Data Buffer (B8)
Power
(PI A16)
Device Access
(PI A17)
(PI ~{RD})
Address Decode
If no devices connected then ommit Device Interrupts (B12)
(PI ~{RAM_{CS}})
If Kernal Mode is required then include: Kernal Mode (B6) Selector 12bit (B14) Selector 12bit (B16) and ommit: 0Ω resistors tying A0 to SA0 ... ~{RAM_{CS}} to S~{RAM} If Kernal Mode is not required then include: 0Ω resistors tying A0 to SA0 ... ~{RAM_{CS}} to S~{RAM} and ommit: Kernal Mode (B6) Sel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
Instruction Code (B17) can be ommitted
(PI ~{ROM_{CS}})

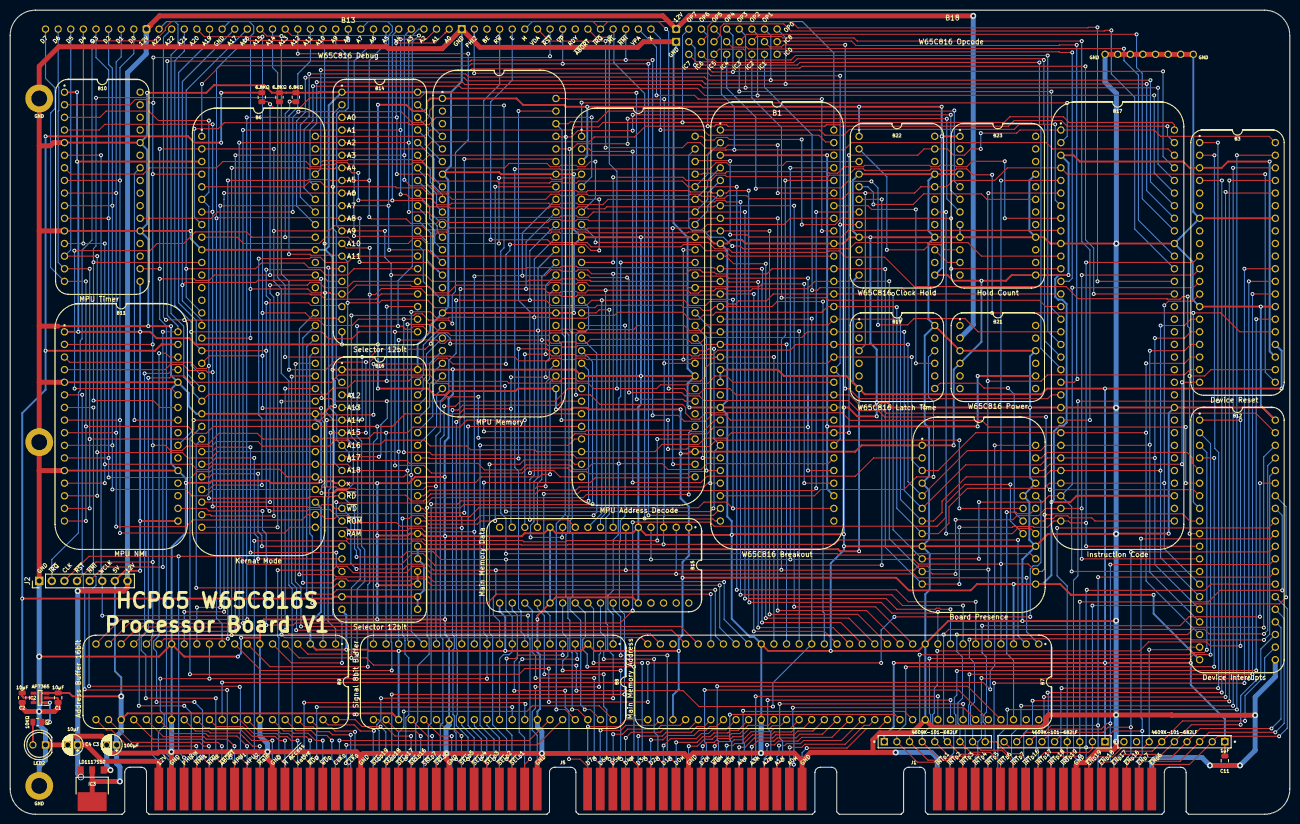
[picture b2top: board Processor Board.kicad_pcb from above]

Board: 2 copper layers, 257.7 x 161.9 mm, 43 parts (0 on the bottom side), 280 nets.
